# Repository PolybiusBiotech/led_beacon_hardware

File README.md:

# LED Beacon 🚀
> Upgrading cheap LED beacons for professional DMX/Art-Net stage control.

 <!-- Tip: Export a nice 3D render from KiCAD -->

## 🚀 Manufacturing Status
- [ ] **Design:** Completed
- [ ] **Prototyping:** In Progress
- [ ] **Production:** Pending

## 📋 Quick Specs
- **MCU:** ESP32-C3-WROOM-02
- **Power:** +12V ±30% @ 2A
- **Connectivity:** DMX512 via 5 pin XLRs and WiFi

## 📂 Project Structure
- `/hardware`: KiCAD project files (Version 9.0.7).
- `/firmware`: PlatformIO project (Arduino/ESP-IDF framework).
- `/mechanical`: 3D-printable housing (.STEP).
- `/docs`: Specification, schematics and design calculations.
<!-- test: for test scripts -->

## 🛠 Setup & Development

### Hardware
- **Library Dependencies:** All footprints/symbols are [local to the repo / use standard KiCAD libs].
- **CI/CD:** Schematics are automatically exported to `/docs` on every push.

### Firmware
1. Open the `/firmware` folder in **VS Code**.
2. Ensure the **PlatformIO** extension is installed.
3. Connect your hardware via USB C port and click **Upload**.

## User Guide

1. Apply power via DC connector, 12V ±30% from a 3A capable supply.
2. Attach to DMX chain with 2x XLR 5pin cables
   * If at the end of the bus use a terminator plug
3. Select a DMX address with the DIP switch
   * This light consumes 20 slots so avoid address above 492.
   * Ensure that this light is >20 slots away from the next lights.
4. Disable the WiFi AP with the DIP switch unless needed for diagnostics
5. Use your DMX controller to send packets on the DMX chain.
   * Slots 1 to 10 control the brightness per channel
     * `0x00` is off
     * `0xFF` is on
   * Slots 11 to 20 control the strobe effect per channel
     * `0x00` is fully on
     * `0x01` strobes at 0.2Hz
     * `0xFF` strobes at 20Hz
6. Enjoy!

---
*Commissioned for Null Sector for EMF Camp 2026.*

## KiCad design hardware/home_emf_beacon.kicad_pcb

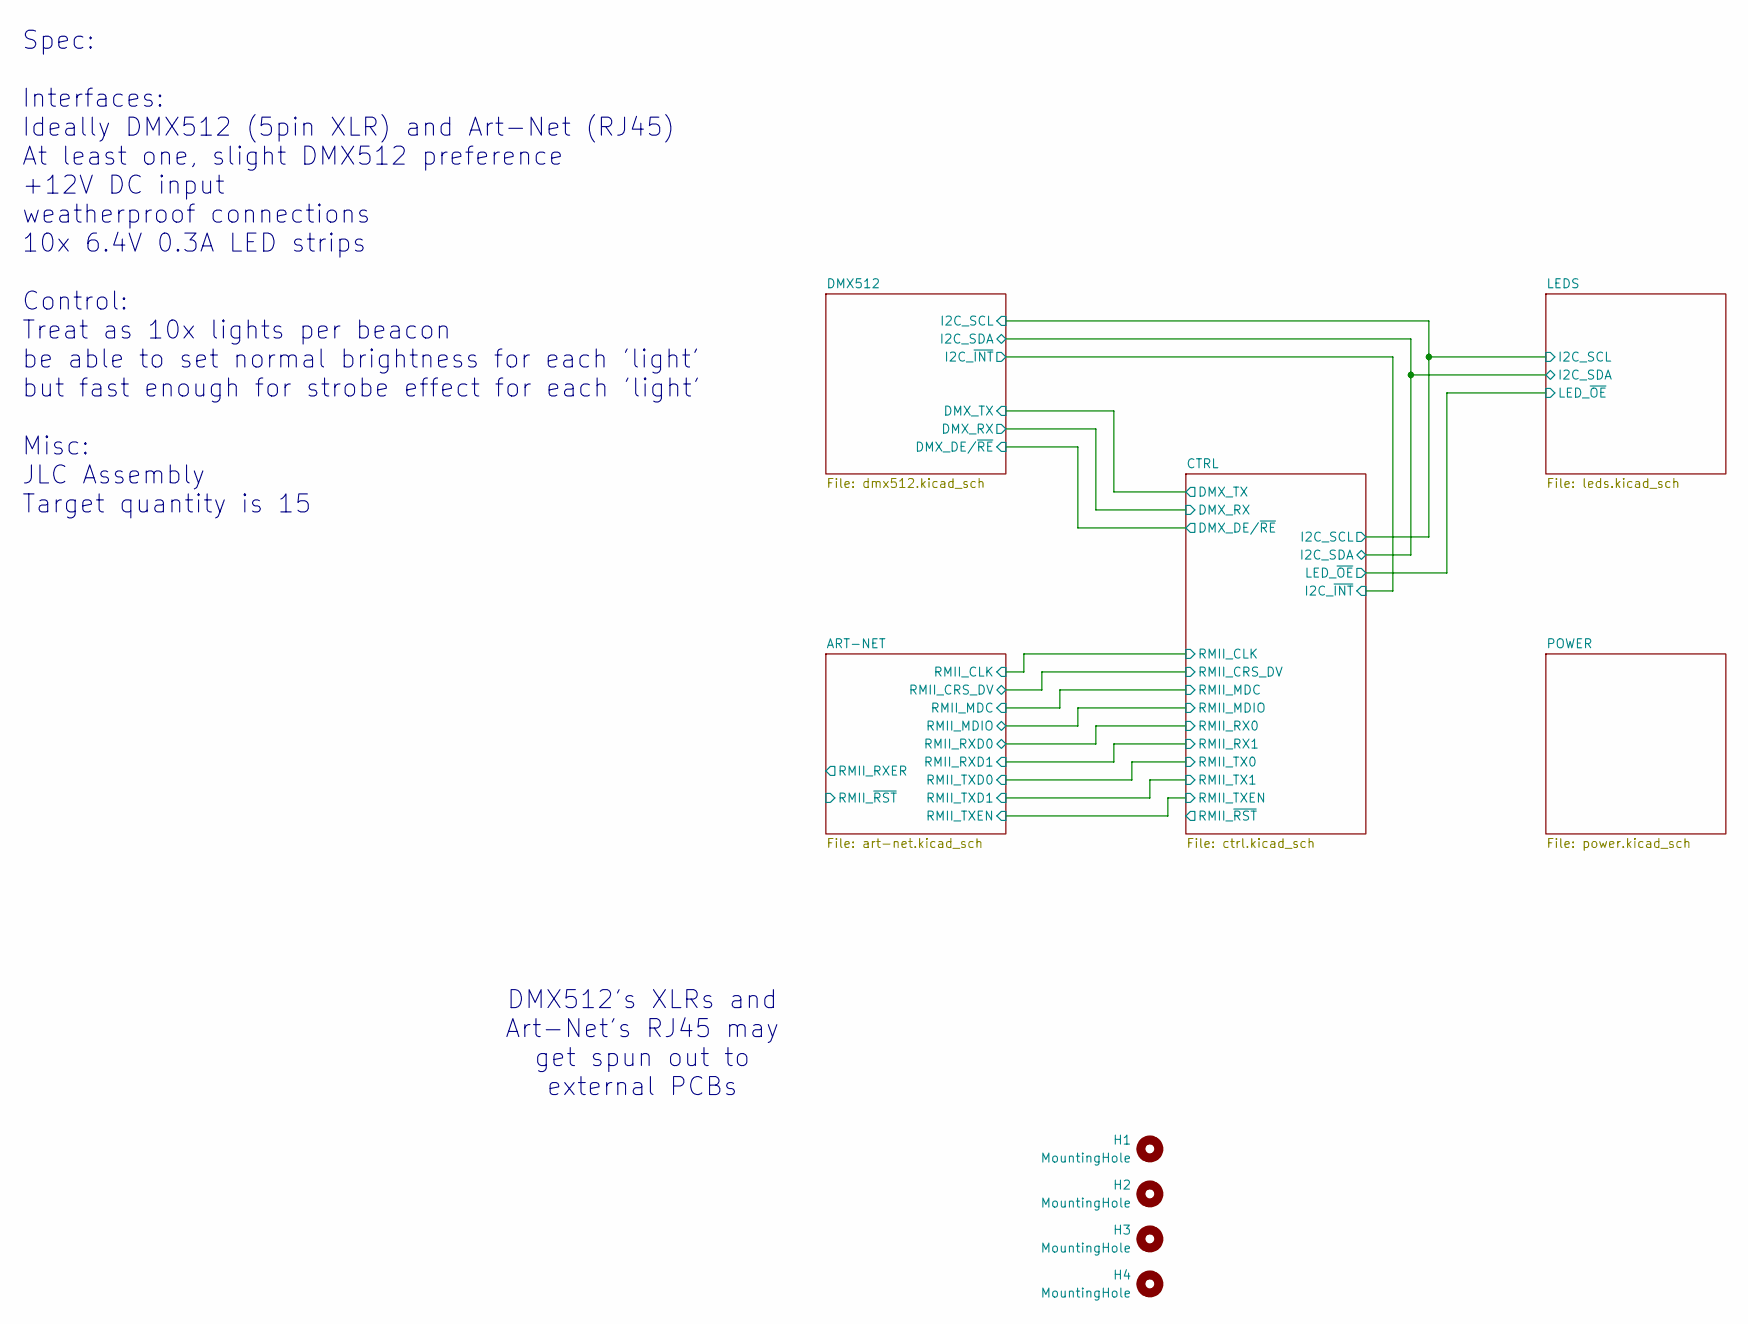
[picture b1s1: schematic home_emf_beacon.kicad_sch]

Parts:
H1, H2, H3, H4: MountingHole; MountingHole_4.3mm_M4

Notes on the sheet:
Spec: Interfaces: Ideally DMX512 (5pin XLR) and Art-Net (RJ45) At least one, slight DMX512 preference +12V DC input weatherproof connections 10x 6.4V 0.3A LED strips Control: Treat as 10x lights per beacon be able to set normal brightness for each 'light' but fast enough for strobe effect for each 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
DMX512's XLRs and Art-Net's RJ45 may get spun out to external PCBs

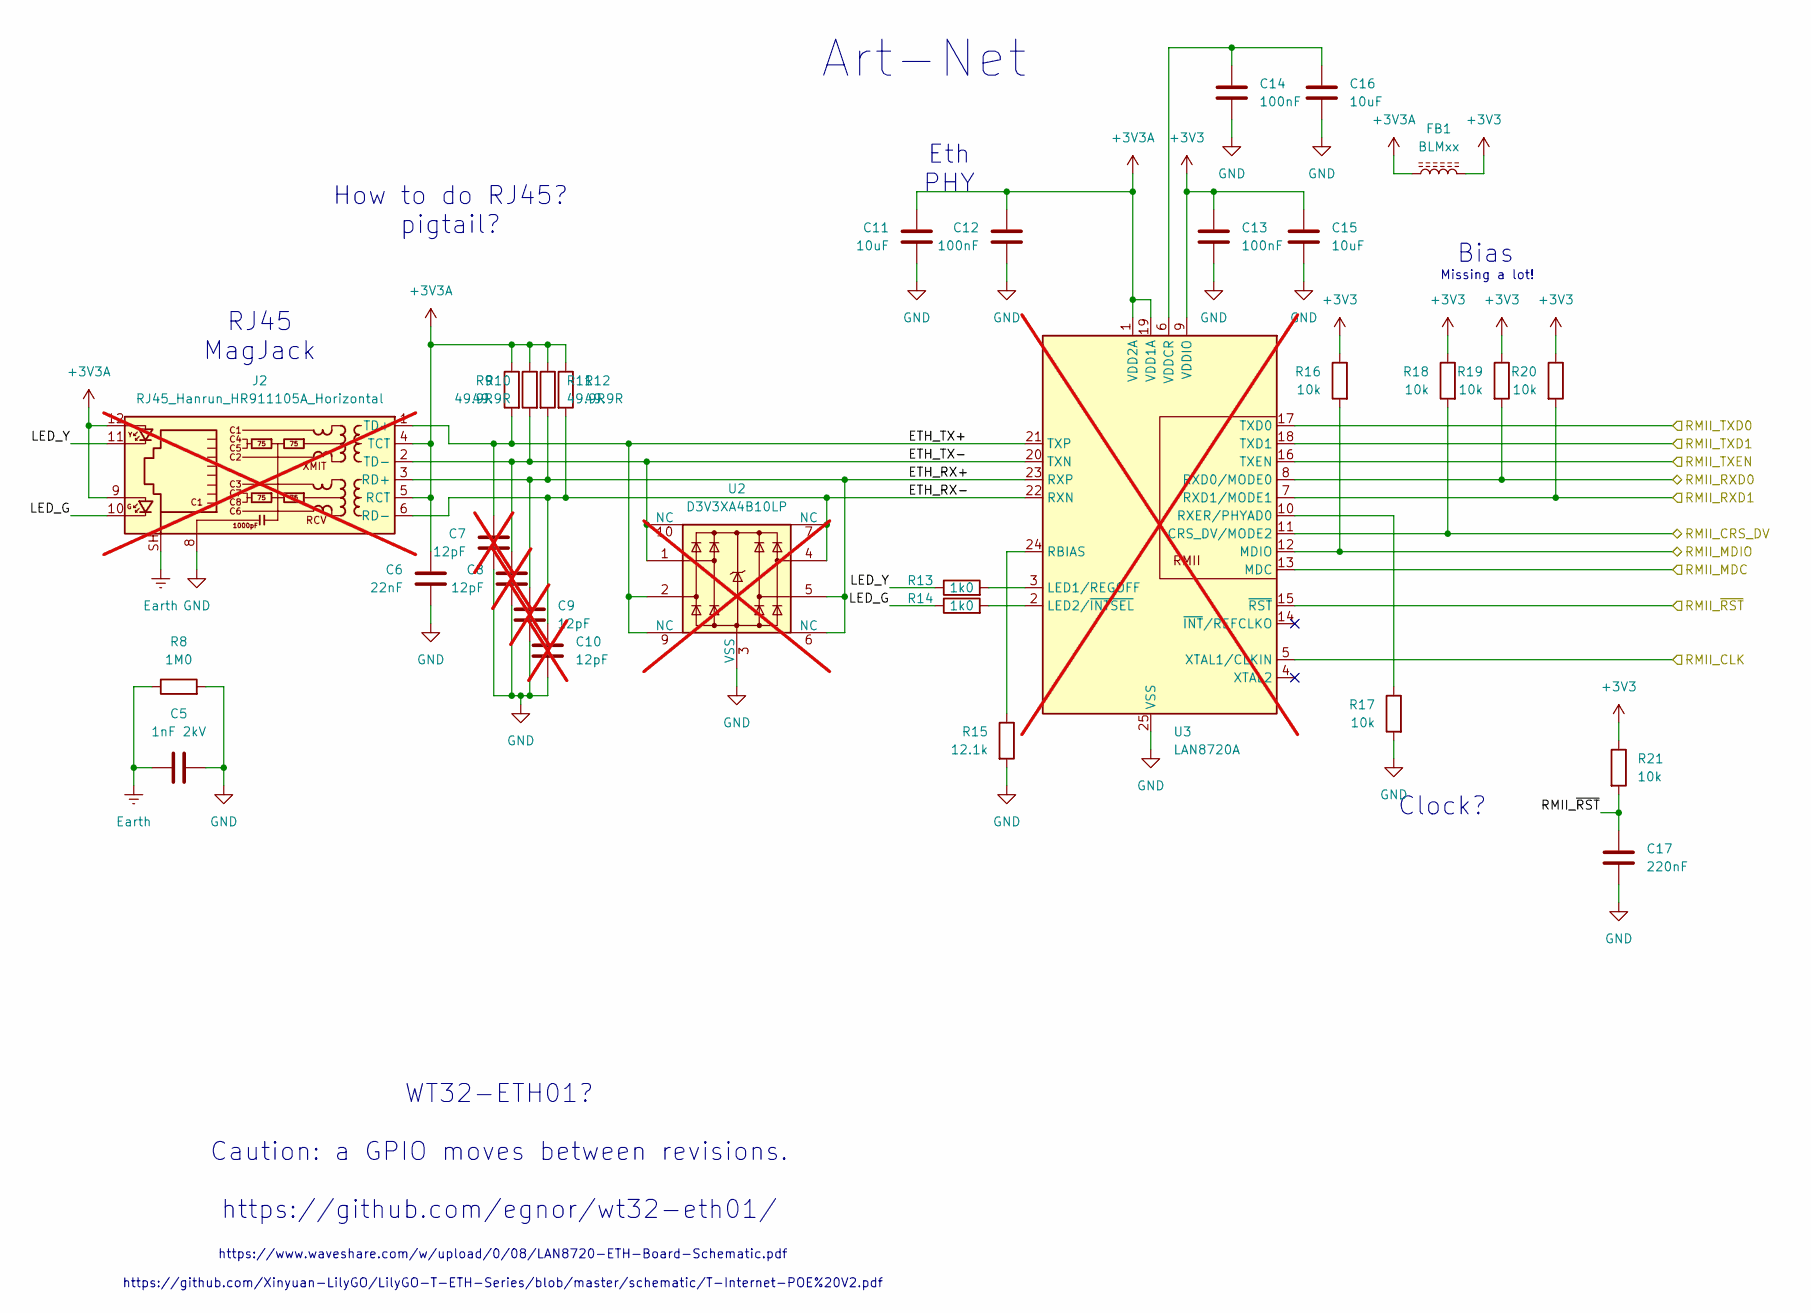
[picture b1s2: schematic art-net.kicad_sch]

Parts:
C5: 1nF 2kV; C_1808_4520Metric
C6: 22nF; C_0603_1608Metric
C7, C8, C9, C10: 12pF; C_0603_1608Metric; not fitted
C11, C15, C16: 10uF; C_0805_2012Metric
C12, C13, C14: 100nF; C_0603_1608Metric
C17: 220nF; C_0603_1608Metric
FB1: BLMxx; L_0603_1608Metric
J2: RJ45_Hanrun_HR911105A_Horizontal; LCSC C12074; not fitted
R8: 1M0; R_1206_3216Metric
R9, R10, R11, R12: 49.9R; R_0603_1608Metric
R13, R14: 1k0; R_0603_1608Metric
R15: 12.1k; R_0603_1608Metric
R16, R17, R18, R19, R20, R21: 10k; R_0603_1608Metric
U2: D3V3XA4B10LP; Diodes_UDFN-10_1x2.5mm_P0.5mm; not fitted
U3: LAN8720A; VQFN-24-1EP_4x4mm_P0.5mm_EP2.5x2.5mm_ThermalVias; not fitted

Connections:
+3V3: C13.2, C15.2, FB1.2, R16.1, R18.1, R19.1, R20.1, R21.1, U3.9 (VDDIO); also elsewhere on the board
+3V3A: C6.1, C11.2, C12.2, FB1.1, J2.4 (TCT), J2.5 (RCT), J2.9, J2.12, R9.1, R10.1, R11.1, R12.1, U3.1 (VDD2A), U3.19 (VDD1A)
/ART-NET/ETH_RX+: C9.1, J2.3 (RD+), R11.2, U2.5, U2.6 (NC), U3.23 (RXP)
/ART-NET/ETH_RX-: C10.1, J2.6 (RD-), R12.2, U2.4, U2.7 (NC), U3.22 (RXN)
/ART-NET/ETH_TX+: C7.1, J2.1 (TD+), R9.2, U2.2, U2.9 (NC), U3.21 (TXP)
/ART-NET/ETH_TX-: C8.1, J2.2 (TD-), R10.2, U2.1, U2.10 (NC), U3.20 (TXN)
/ART-NET/LED_G: J2.10, R14.1
/ART-NET/LED_Y: J2.11, R13.1
/ART-NET/RMII_~RST: C17.1, R21.2, U3.15 (~RST)
/CTRL/RMII_CLK: U3.5 (XTAL1/CLKIN); also elsewhere on the board
/CTRL/RMII_CRS_DV: R18.2, U3.11 (CRS_DV/MODE2); also elsewhere on the board
/CTRL/RMII_MDC: U3.13 (MDC); also elsewhere on the board
/CTRL/RMII_MDIO: R16.2, U3.12 (MDIO); also elsewhere on the board
/CTRL/RMII_RX0: R19.2, U3.8 (RXD0/MODE0); also elsewhere on the board
/CTRL/RMII_RX1: R20.2, U3.7 (RXD1/MODE1); also elsewhere on the board
/CTRL/RMII_TX0: U3.17 (TXD0); also elsewhere on the board
/CTRL/RMII_TX1: U3.18 (TXD1); also elsewhere on the board
/CTRL/RMII_TXEN: U3.16 (TXEN); also elsewhere on the board
Earth: C5.1, J2.SH, R8.1
GND: C5.2, C6.2, C7.2, C8.2, C9.2, C10.2, C11.1, C12.1, C13.1, C14.1, C15.1, C16.1, C17.2, J2.8, R8.2, R15.2, R17.2, U2.3 (VSS), U2.8 (VSS), U3.25 (VSS); also elsewhere on the board
unnamed: R13.2, U3.3 (LED1/REGOFF)
unnamed: R14.2, U3.2 (LED2/~INTSEL)
unnamed: R15.1, U3.24 (RBIAS)
unnamed: R17.1, U3.10 (RXER/PHYAD0)
unnamed: C14.2, C16.2, U3.6 (VDDCR)

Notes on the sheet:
How to do RJ45? pigtail?
Bias
WT32-ETH01? Caution: a GPIO moves between revisions. https://github.com/egnor/wt32-eth01/
https://www.waveshare.com/w/upload/0/08/LAN8720-ETH-Board-Schematic.pdf https://github.com/Xinyuan-LilyGO/LilyGO-T-ETH-Series/blob/master/schematic/T-Internet-POE%20V2.pdf
RJ45 MagJack
Art-Net
Eth PHY
Missing a lot!
Clock?

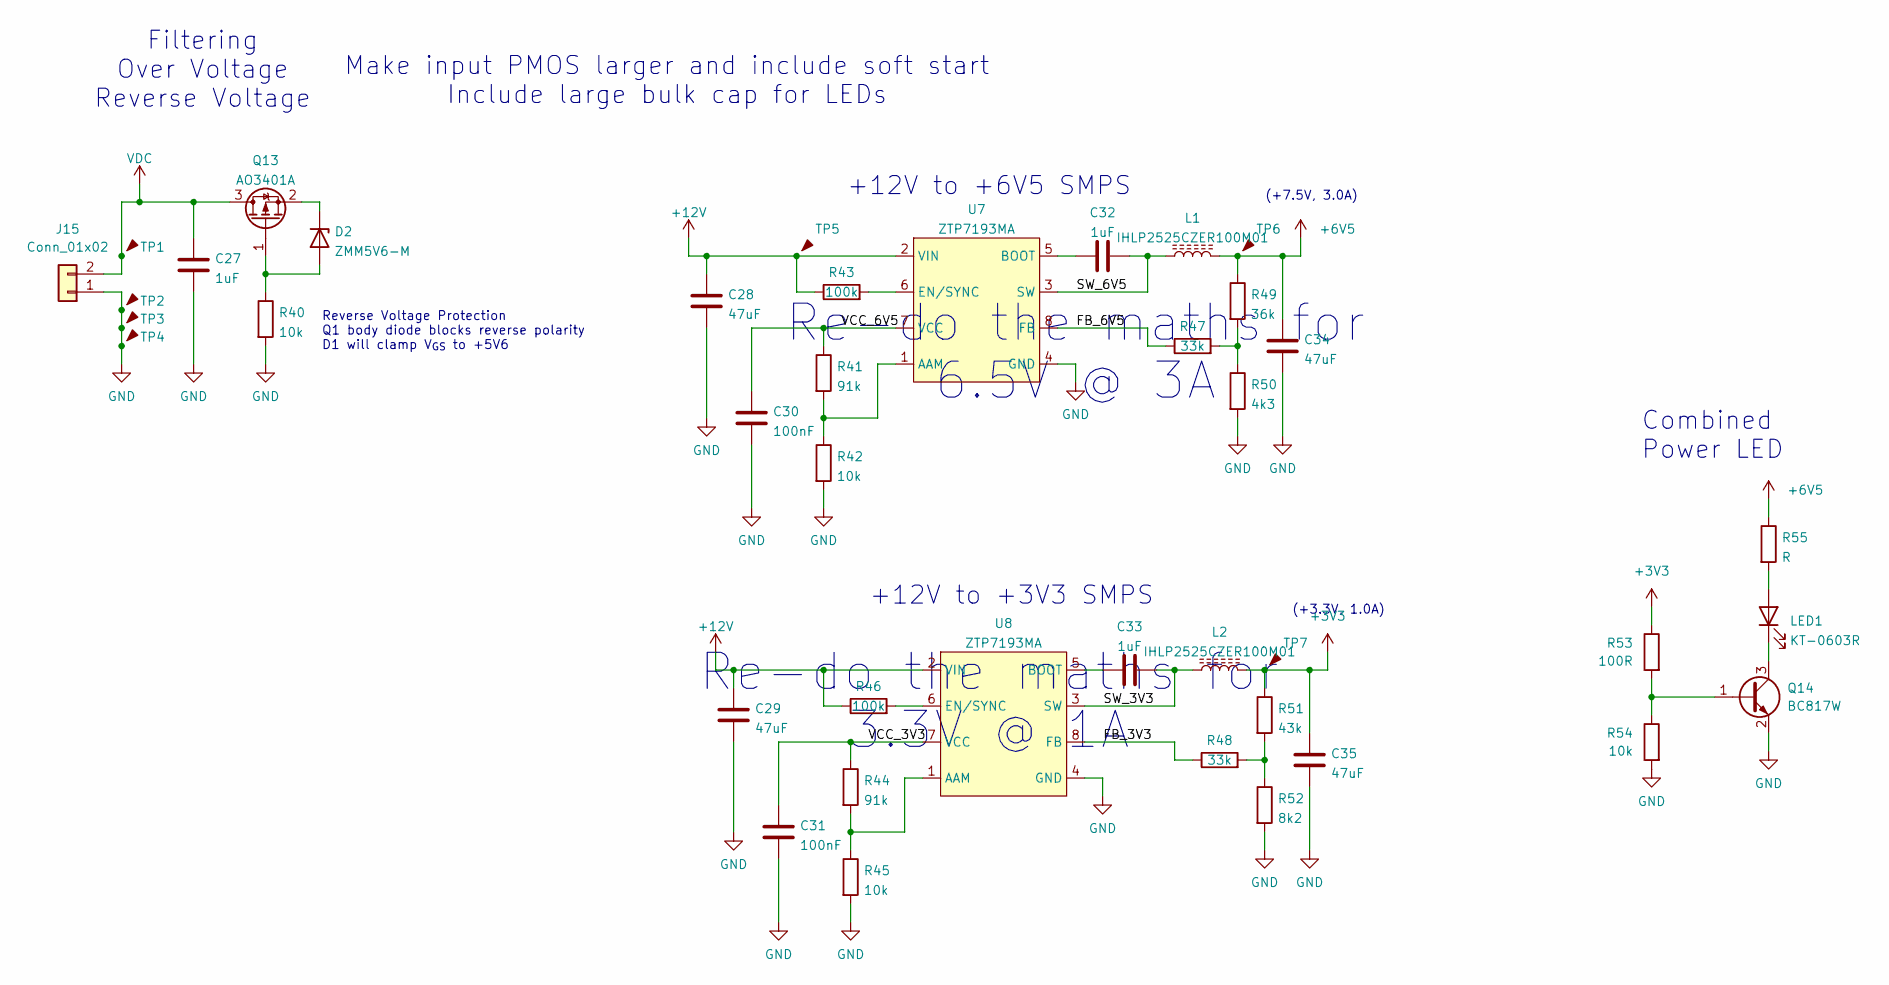
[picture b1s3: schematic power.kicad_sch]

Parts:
C27, C32, C33: 1uF; C_0603_1608Metric; Voltage 50V; LCSC C15849
C28, C29, C34, C35: 47uF; C_1210_3225Metric; Voltage 25V; LCSC C77101
C30, C31: 100nF; C_0603_1608Metric; Voltage 50V; LCSC C14663
D2: ZMM5V6-M; D_MiniMELF; LCSC C8062
J15: Conn_01x02; PhoenixContact_MSTBVA_2,5_2-G-5,08_1x02_P5.08mm_Vertical
L1, L2: IHLP2525CZER100M01; L_Vishay_IHLP-2525; LCSC C540965
LED1: KT-0603R; LED_0603_1608Metric; LCSC C2286
Q13: AO3401A; SOT-23; LCSC C15127
Q14: BC817W; SOT-323_SC-70
R40, R42, R45: 10k; R_0603_1608Metric; LCSC C25804
R41, R44: 91k; R_0603_1608Metric; LCSC C23265
R43, R46: 100k; R_0603_1608Metric; LCSC C25803
R47, R48: 33k; R_0603_1608Metric; LCSC C4216
R49: 36k; R_0603_1608Metric; LCSC C23147
R50: 4k3; R_0603_1608Metric; LCSC C23159
R51: 43k; R_0603_1608Metric; LCSC C23172
R52: 8k2; R_0603_1608Metric; LCSC C25981
R53: 100R; R_0603_1608Metric
R54: 10k; R_0603_1608Metric
R55: R; R_0603_1608Metric
TP1, TP2, TP3, TP4, TP5, TP6, TP7: TestPoint; TestPoint_Pad_D1.5mm
U7, U8: ZTP7193MA; SOT-23-8; LCSC C481284

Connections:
+3V3: C35.1, L2.2, R51.1, R53.1, TP7.1; also elsewhere on the board
+6V5: C34.1, L1.2, R49.1, R55.1, TP6.1; also elsewhere on the board
+12V: C28.1, C29.1, R43.1, R46.1, TP5.1, U7.2 (VIN), U8.2 (VIN)
/POWER/FB_3V3: R48.1, U8.8 (FB)
/POWER/FB_6V5: R47.1, U7.8 (FB)
/POWER/SW_3V3: C33.2, L2.1, U8.3 (SW)
/POWER/SW_6V5: C32.2, L1.1, U7.3 (SW)
/POWER/VCC_3V3: C31.2, R44.1, U8.7 (VCC)
/POWER/VCC_6V5: C30.2, R41.1, U7.7 (VCC)
GND: C27.2, C28.2, C29.2, C30.1, C31.1, C34.2, C35.2, J15.1, Q14.2 (E), R40.2, R42.2, R45.2, R50.2, R52.2, R54.2, TP2.1, TP3.1, TP4.1, U7.4 (GND), U8.4 (GND); also elsewhere on the board
unnamed: D2.2 (A), Q13.1 (G), R40.1
unnamed: D2.1 (K), Q13.2 (S)
unnamed: LED1.2 (A), R55.2
unnamed: LED1.1 (K), Q14.3 (C)
unnamed: Q14.1 (B), R53.2, R54.1
unnamed: R47.2, R49.2, R50.1
unnamed: R48.2, R51.2, R52.1
unnamed: R41.2, R42.1, U7.1 (AAM)
unnamed: C32.1, U7.5 (BOOT)
unnamed: R43.2, U7.6 (EN/SYNC)
unnamed: R44.2, R45.1, U8.1 (AAM)
unnamed: C33.1, U8.5 (BOOT)
unnamed: R46.2, U8.6 (EN/SYNC)
VDC: C27.1, J15.2, Q13.3 (D), TP1.1

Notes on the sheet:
Make input PMOS larger and include soft start Include large bulk cap for LEDs
(+7.5V, 3.0A)
Re-do the maths for 3.3V @ 1A
Re-do the maths for 6.5V @ 3A
Filtering Over Voltage Reverse Voltage
Combined Power LED
(+3.3V, 1.0A)
+12V to +3V3 SMPS
+12V to +6V5 SMPS
Reverse Voltage Protection Q1 body diode blocks reverse polarity D1 will clamp V_{GS} to +5V6

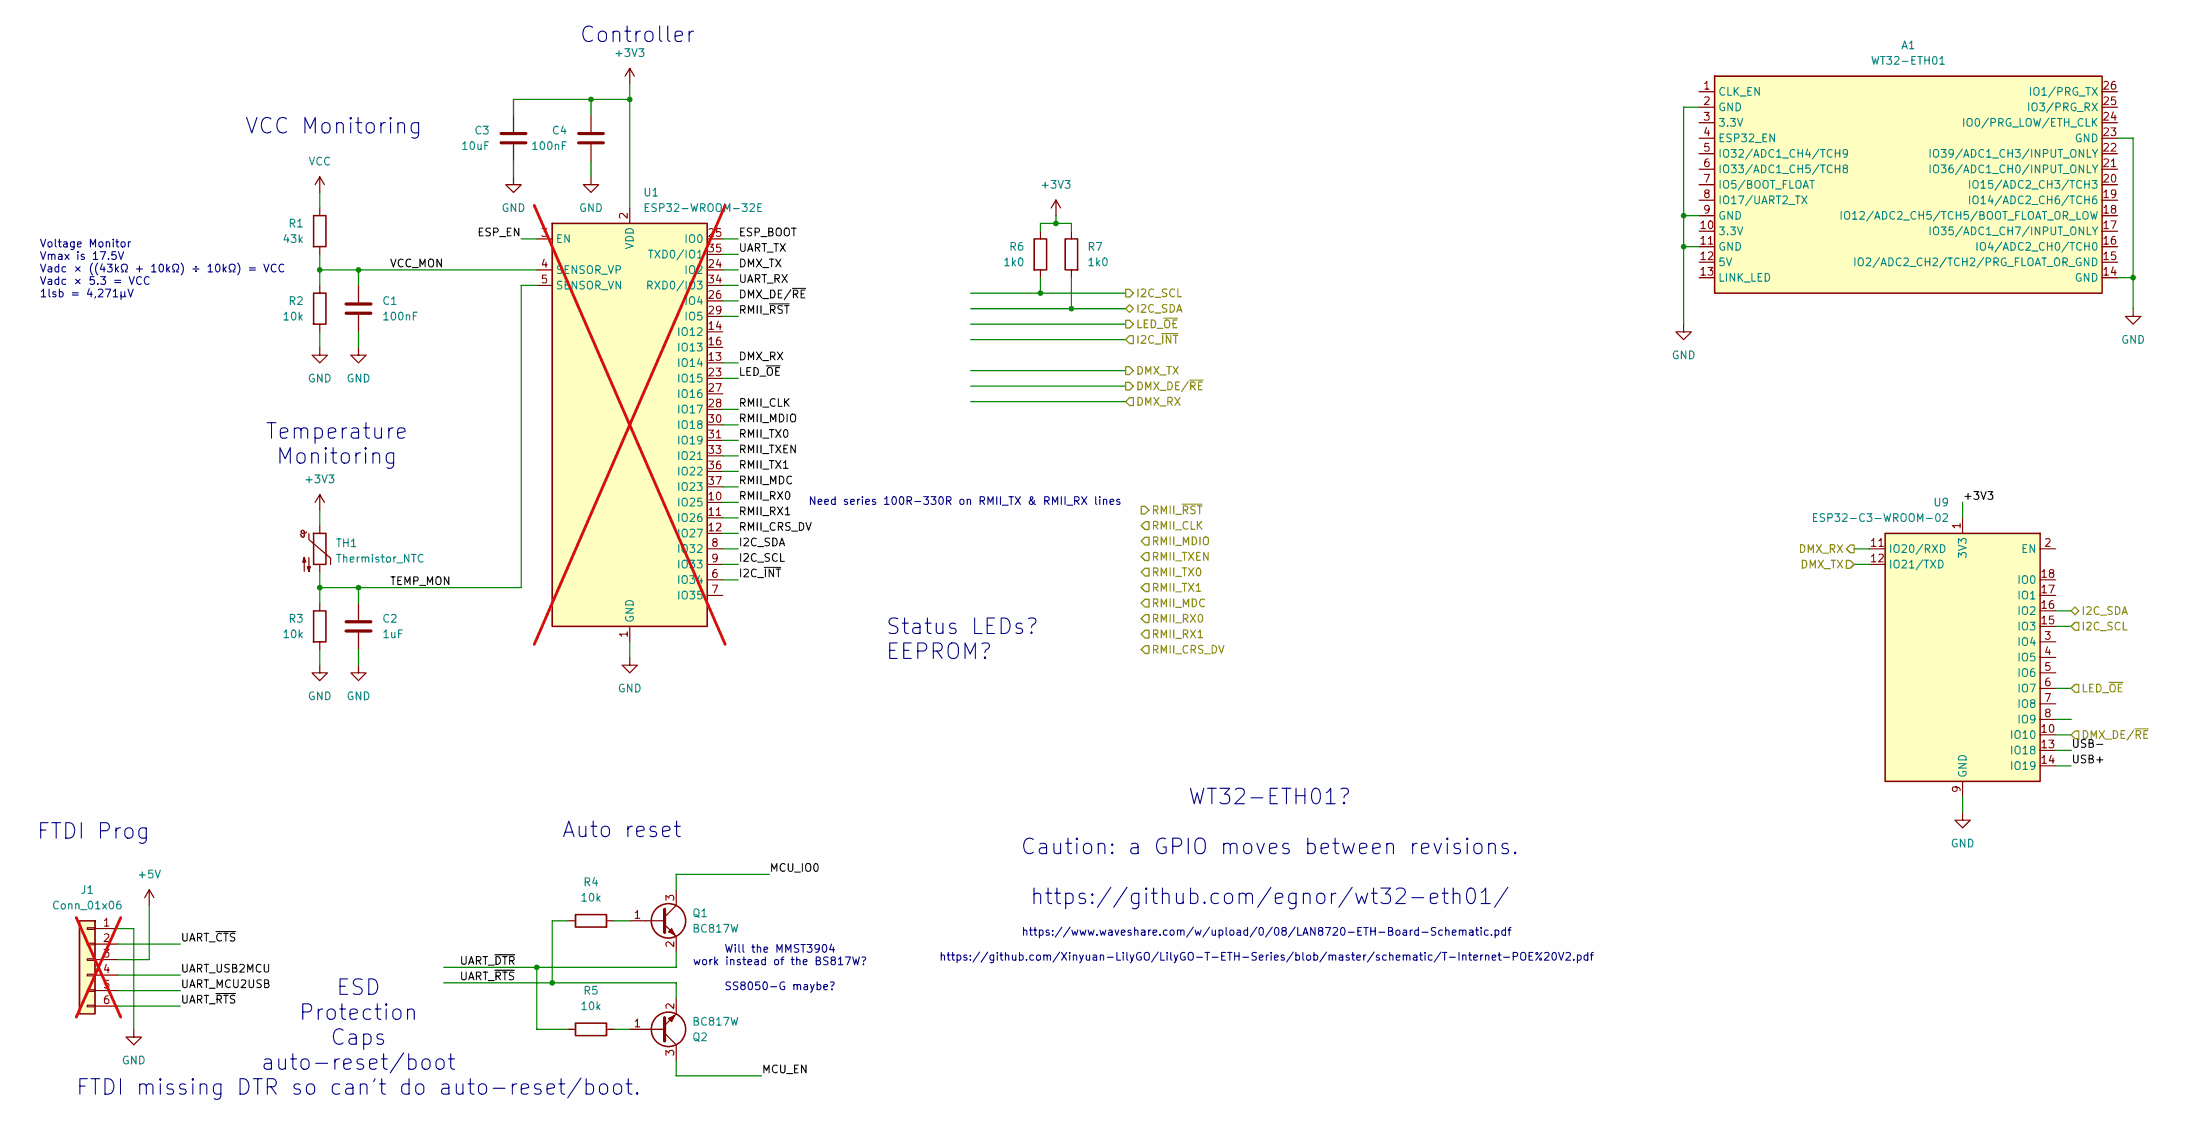
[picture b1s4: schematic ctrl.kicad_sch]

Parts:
A1: WT32-ETH01
C1, C4: 100nF; C_0603_1608Metric
C2: 1uF; C_0603_1608Metric
C3: 10uF; C_0805_2012Metric
J1: Conn_01x06; PinHeader_1x06_P2.54mm_Vertical; not fitted
Q1, Q2: BC817W; SOT-323_SC-70
R1: 43k; R_0603_1608Metric
R2, R3, R4, R5: 10k; R_0603_1608Metric
R6, R7: 1k0; R_0603_1608Metric
TH1: Thermistor_NTC; R_0603_1608Metric
U1: ESP32-WROOM-32E; ESP32-WROOM-32D; not fitted
U9: ESP32-C3-WROOM-02

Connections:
+3V3: C3.1, C4.1, R6.1, R7.1, TH1.1, U1.2 (VDD), U9.1 (3V3); also elsewhere on the board
+5V: J1.3
/CTRL/DMX_DE/~RE: U1.26 (IO4), U9.10 (IO10); also elsewhere on the board
/CTRL/DMX_RX: U1.13 (IO14), U9.11 (IO20/RXD); also elsewhere on the board
/CTRL/DMX_TX: U1.24 (IO2), U9.12 (IO21/TXD); also elsewhere on the board
/CTRL/ESP_BOOT: U1.25 (IO0)
/CTRL/ESP_EN: U1.3 (EN)
/CTRL/I2C_SCL: R6.2, U1.9 (IO33), U9.15 (IO3); also elsewhere on the board
/CTRL/I2C_SDA: R7.2, U1.8 (IO32), U9.16 (IO2); also elsewhere on the board
/CTRL/I2C_~INT: U1.6 (IO34); also elsewhere on the board
/CTRL/LED_~OE: U1.23 (IO15), U9.6 (IO7); also elsewhere on the board
/CTRL/MCU_EN: Q2.3 (C)
/CTRL/MCU_IO0: Q1.3 (C)
/CTRL/RMII_CLK: U1.28 (IO17); also elsewhere on the board
/CTRL/RMII_CRS_DV: U1.12 (IO27); also elsewhere on the board
/CTRL/RMII_MDC: U1.37 (IO23); also elsewhere on the board
/CTRL/RMII_MDIO: U1.30 (IO18); also elsewhere on the board
/CTRL/RMII_RX0: U1.10 (IO25); also elsewhere on the board
/CTRL/RMII_RX1: U1.11 (IO26); also elsewhere on the board
/CTRL/RMII_TX0: U1.31 (IO19); also elsewhere on the board
/CTRL/RMII_TX1: U1.36 (IO22); also elsewhere on the board
/CTRL/RMII_TXEN: U1.33 (IO21); also elsewhere on the board
/CTRL/RMII_~RST: U1.29 (IO5)
/CTRL/TEMP_MON: C2.1, R3.1, TH1.2, U1.5 (SENSOR_VN)
/CTRL/UART_MCU2USB: J1.5
/CTRL/UART_RX: U1.34 (RXD0/IO3)
/CTRL/UART_TX: U1.35 (TXD0/IO1)
/CTRL/UART_USB2MCU: J1.4
/CTRL/UART_~CTS: J1.2
/CTRL/UART_~DTR: Q1.2 (E), R5.1
/CTRL/UART_~RTS: J1.6, Q2.2 (E), R4.1
/CTRL/USB+: U9.14 (IO19)
/CTRL/USB-: U9.13 (IO18)
/CTRL/VCC_MON: C1.1, R1.2, R2.1, U1.4 (SENSOR_VP)
GND: A1.2 (GND), A1.9 (GND), A1.11 (GND), A1.14 (GND), A1.23 (GND), C1.2, C2.2, C3.2, C4.2, J1.1, R2.2, R3.2, U1.1 (GND), U1.15 (GND), U1.38 (GND), U1.39 (GND), U9.9 (GND), U9.19 (GND); also elsewhere on the board
unnamed: Q1.1 (B), R4.2
unnamed: Q2.1 (B), R5.2
VCC: R1.1

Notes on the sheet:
Auto reset
Status LEDs? EEPROM?
WT32-ETH01? Caution: a GPIO moves between revisions. https://github.com/egnor/wt32-eth01/
VCC Monitoring
Need series 100R-330R on RMII_TX & RMII_RX lines
Will the MMST3904 work instead of the BS817W? SS8050-G maybe?
https://www.waveshare.com/w/upload/0/08/LAN8720-ETH-Board-Schematic.pdf https://github.com/Xinyuan-LilyGO/LilyGO-T-ETH-Series/blob/master/schematic/T-Internet-POE%20V2.pdf
Temperature Monitoring
Controller
FTDI Prog
ESD Protection Caps auto-reset/boot FTDI missing DTR so can't do auto-reset/boot.
Voltage Monitor Vmax is 17.5V Vadc × ((43kΩ + 10kΩ) ÷ 10kΩ) = VCC Vadc × 5.3 = VCC 1lsb = 4,271μV

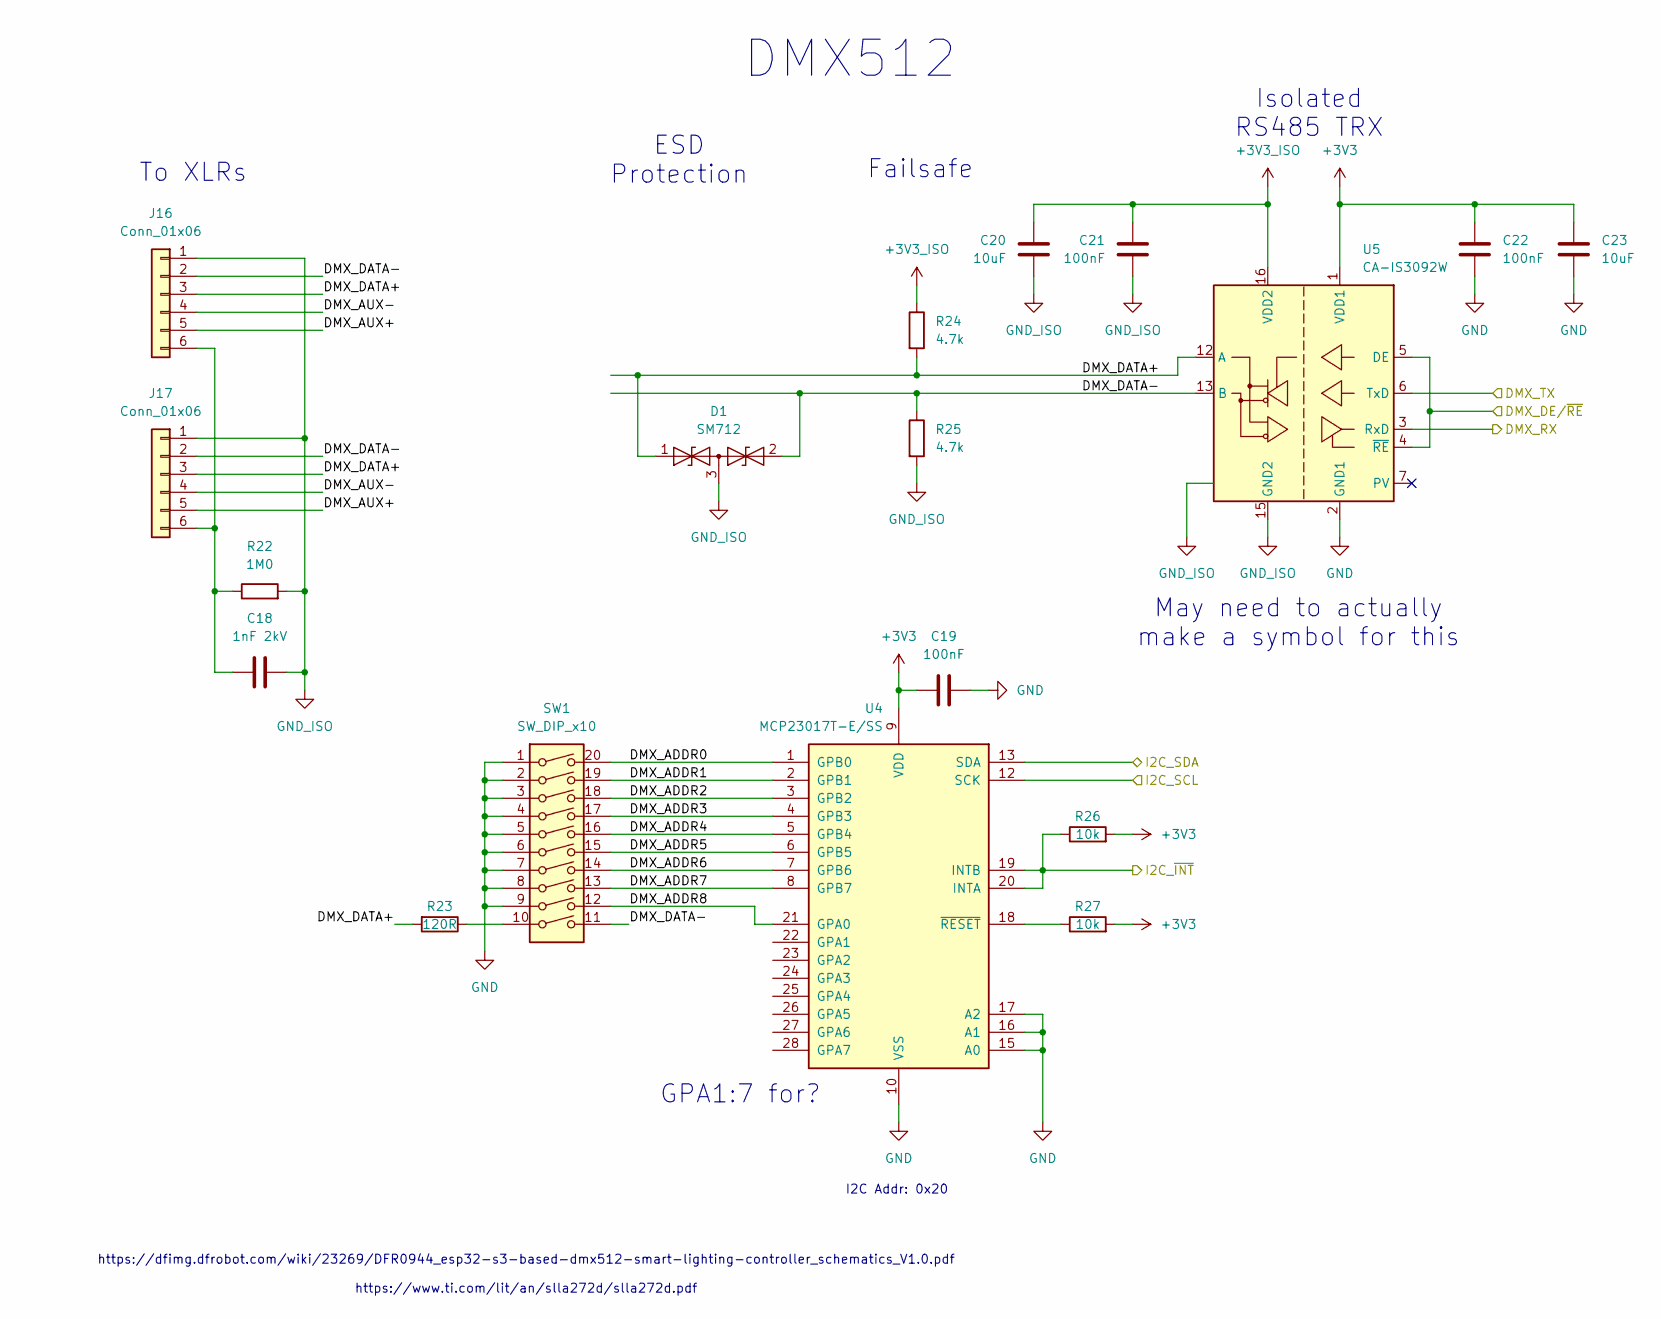
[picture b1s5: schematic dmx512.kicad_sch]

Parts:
C18: 1nF 2kV; C_1808_4520Metric
C19, C21, C22: 100nF; C_0603_1608Metric
C20, C23: 10uF; C_0805_2012Metric
D1: SM712; SOT-23; LCSC C7420375
J16, J17: Conn_01x06; JST_PH_B6B-PH-K_1x06_P2.00mm_Vertical
R22: 1M0; R_1206_3216Metric
R23: 120R; R_0805_2012Metric_Pad1.20x1.40mm_HandSolder
R24, R25: 4.7k; R_0603_1608Metric
R26, R27: 10k; R_0603_1608Metric
SW1: SW_DIP_x10; SW_DIP_SPSTx10_Slide_6.7x26.96mm_W7.62mm_P2.54mm_LowProfile; LCSC C509577
U4: MCP23017T-E/SS; SSOP-28_5.3x10.2mm_P0.65mm; LCSC C558584
U5: CA-IS3092W; SOIC-16W_7.5x10.3mm_P1.27mm; LCSC C2890051

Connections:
+3V3: C19.2, C22.1, C23.1, R26.2, R27.2, U4.9 (VDD), U5.1 (VDD1); also elsewhere on the board
+3V3_ISO: C20.1, C21.1, R24.1, U5.16 (VDD2)
/CTRL/DMX_DE/~RE: U5.4 (~RE), U5.5 (DE); also elsewhere on the board
/CTRL/DMX_RX: U5.3 (RxD); also elsewhere on the board
/CTRL/DMX_TX: U5.6 (TxD); also elsewhere on the board
/CTRL/I2C_SCL: U4.12 (SCK); also elsewhere on the board
/CTRL/I2C_SDA: U4.13 (SDA); also elsewhere on the board
/CTRL/I2C_~INT: R26.1, U4.19 (INTB), U4.20 (INTA); also elsewhere on the board
/DMX512/DMX_ADDR0: SW1.20, U4.1 (GPB0)
/DMX512/DMX_ADDR1: SW1.19, U4.2 (GPB1)
/DMX512/DMX_ADDR2: SW1.18, U4.3 (GPB2)
/DMX512/DMX_ADDR3: SW1.17, U4.4 (GPB3)
/DMX512/DMX_ADDR4: SW1.16, U4.5 (GPB4)
/DMX512/DMX_ADDR5: SW1.15, U4.6 (GPB5)
/DMX512/DMX_ADDR6: SW1.14, U4.7 (GPB6)
/DMX512/DMX_ADDR7: SW1.13, U4.8 (GPB7)
/DMX512/DMX_ADDR8: SW1.12, U4.21 (GPA0)
/DMX512/DMX_AUX+: J16.5, J17.5
/DMX512/DMX_AUX-: J16.4, J17.4
/DMX512/DMX_DATA+: D1.1 (A1), J16.3, J17.3, R23.2, R24.2, U5.12 (A)
/DMX512/DMX_DATA-: D1.2 (A2), J16.2, J17.2, R25.1, SW1.11, U5.13 (B)
GND: C19.1, C22.2, C23.2, SW1.1, SW1.2, SW1.3, SW1.4, SW1.5, SW1.6, SW1.7, SW1.8, SW1.9, U4.10 (VSS), U4.15 (A0), U4.16 (A1), U4.17 (A2), U5.2 (GND1), U5.8 (GND1); also elsewhere on the board
GND_ISO: C18.2, C20.2, C21.2, D1.3 (common), J16.1, J17.1, R22.2, R25.2, U5.9 (GND2), U5.15 (GND2)
unnamed: C18.1, J16.6, J17.6, R22.1
unnamed: R23.1, SW1.10
unnamed: R27.1, U4.18 (~RESET)

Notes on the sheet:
May need to actually make a symbol for this
I2C Addr: 0x20
Failsafe
DMX512
https://dfimg.dfrobot.com/wiki/23269/DFR0944_esp32-s3-based-dmx512-smart-lighting-controller_schematics_V1.0.pdf https://www.ti.com/lit/an/slla272d/slla272d.pdf
To XLRs
ESD Protection
GPA1:7 for?
Isolated RS485 TRX

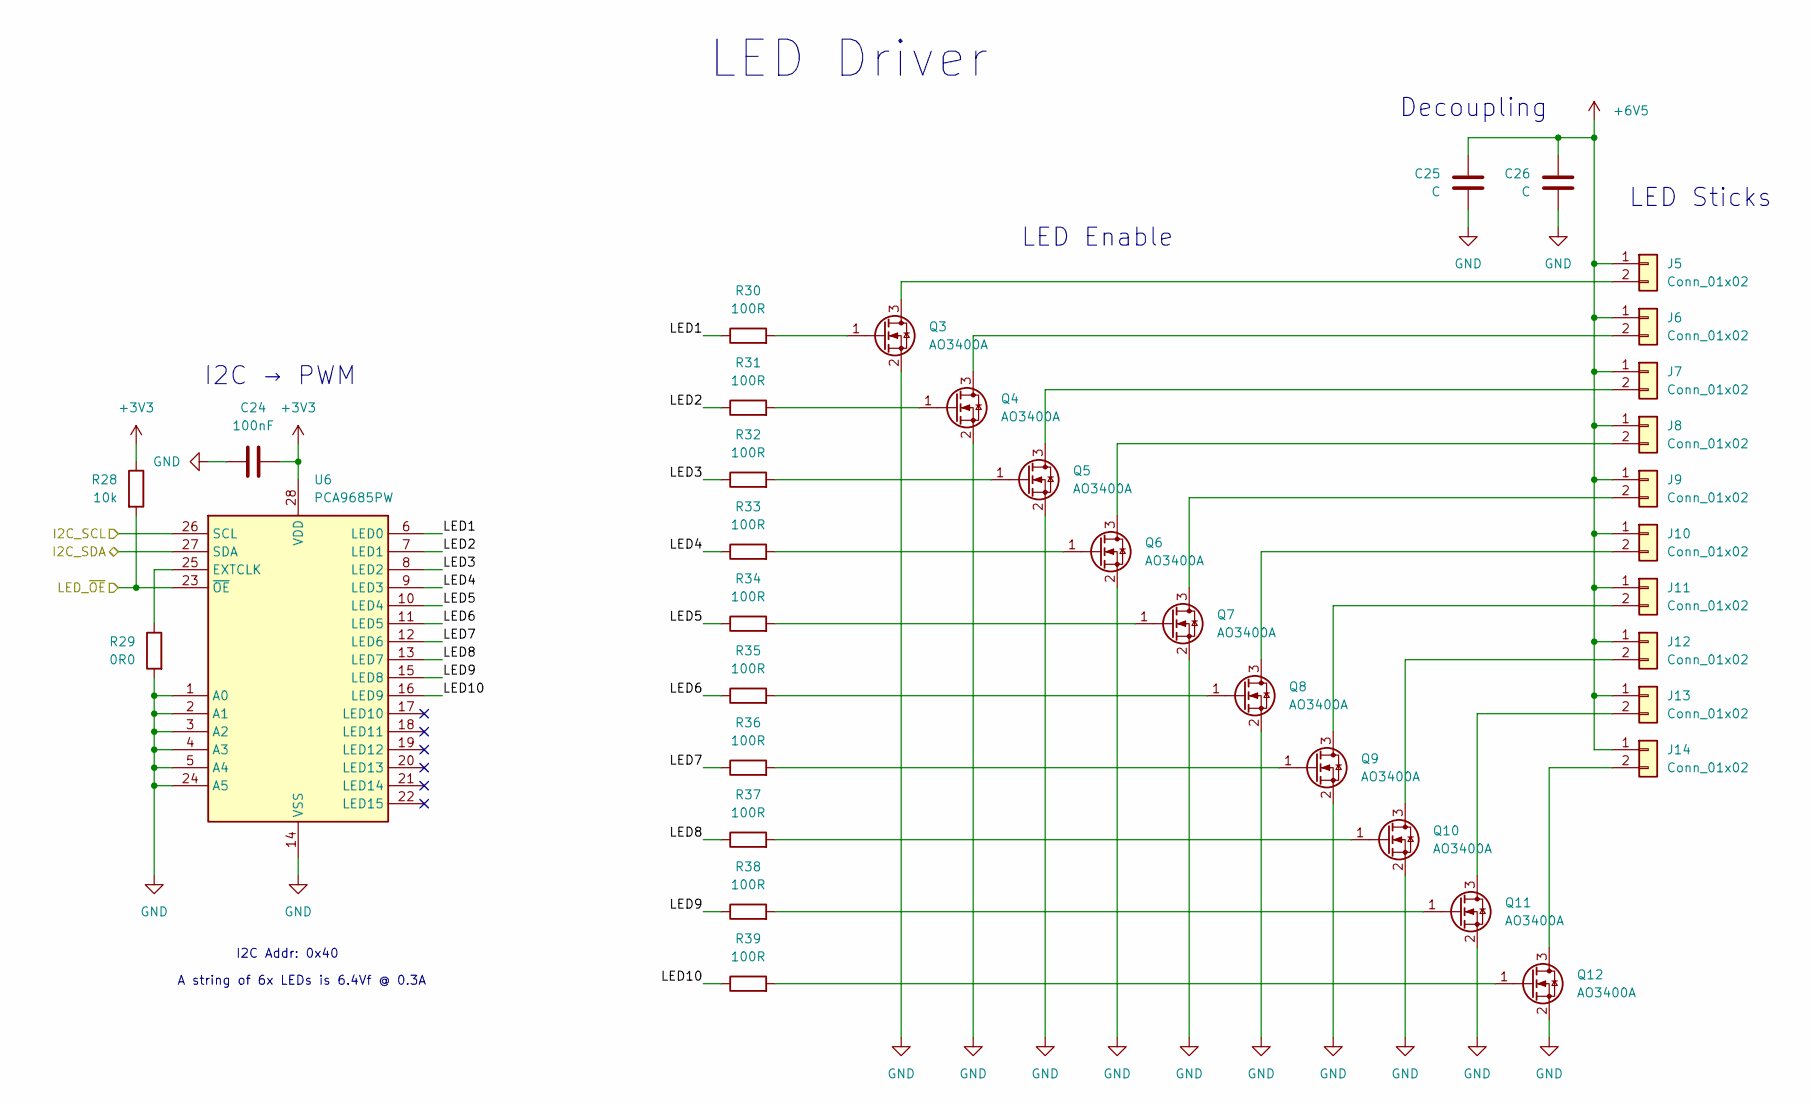
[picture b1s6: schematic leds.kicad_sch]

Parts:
C24: 100nF; C_0603_1608Metric
C25, C26: C
J5, J6, J7, J8, J9, J10, J11, J12, J13, J14: Conn_01x02; LED_Stick
Q3, Q4, Q5, Q6, Q7, Q8, Q9, Q10, Q11, Q12: AO3400A; SOT-23; LCSC C20917
R28: 10k; R_0603_1608Metric
R29: 0R0; R_0603_1608Metric
R30, R31, R32, R33, R34, R35, R36, R37, R38, R39: 100R; R_0603_1608Metric
U6: PCA9685PW; TSSOP-28_4.4x9.7mm_P0.65mm; LCSC C92206

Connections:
+3V3: C24.2, R28.1, U6.28 (VDD); also elsewhere on the board
+6V5: C25.1, C26.1, J5.1, J6.1, J7.1, J8.1, J9.1, J10.1, J11.1, J12.1, J13.1, J14.1; also elsewhere on the board
/CTRL/I2C_SCL: U6.26 (SCL); also elsewhere on the board
/CTRL/I2C_SDA: U6.27 (SDA); also elsewhere on the board
/CTRL/LED_~OE: R28.2, U6.23 (~OE); also elsewhere on the board
/LEDS/LED1: R30.1, U6.6 (LED0)
/LEDS/LED2: R31.1, U6.7 (LED1)
/LEDS/LED3: R32.1, U6.8 (LED2)
/LEDS/LED4: R33.1, U6.9 (LED3)
/LEDS/LED5: R34.1, U6.10 (LED4)
/LEDS/LED6: R35.1, U6.11 (LED5)
/LEDS/LED7: R36.1, U6.12 (LED6)
/LEDS/LED8: R37.1, U6.13 (LED7)
/LEDS/LED9: R38.1, U6.15 (LED8)
/LEDS/LED10: R39.1, U6.16 (LED9)
GND: C24.1, C25.2, C26.2, Q3.2 (S), Q4.2 (S), Q5.2 (S), Q6.2 (S), Q7.2 (S), Q8.2 (S), Q9.2 (S), Q10.2 (S), Q11.2 (S), Q12.2 (S), R29.2, U6.1 (A0), U6.2 (A1), U6.3 (A2), U6.4 (A3), U6.5 (A4), U6.14 (VSS), U6.24 (A5); also elsewhere on the board
unnamed: J5.2, Q3.3 (D)
unnamed: J6.2, Q4.3 (D)
unnamed: J7.2, Q5.3 (D)
unnamed: J8.2, Q6.3 (D)
unnamed: J9.2, Q7.3 (D)
unnamed: J10.2, Q8.3 (D)
unnamed: J11.2, Q9.3 (D)
unnamed: J12.2, Q10.3 (D)
unnamed: J13.2, Q11.3 (D)
unnamed: J14.2, Q12.3 (D)
unnamed: Q3.1 (G), R30.2
unnamed: Q4.1 (G), R31.2
unnamed: Q5.1 (G), R32.2
unnamed: Q6.1 (G), R33.2
unnamed: Q7.1 (G), R34.2
unnamed: Q8.1 (G), R35.2
unnamed: Q9.1 (G), R36.2
unnamed: Q10.1 (G), R37.2
unnamed: Q11.1 (G), R38.2
unnamed: Q12.1 (G), R39.2
unnamed: R29.1, U6.25 (EXTCLK)

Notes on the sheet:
I2C → PWM
A string of 6x LEDs is 6.4Vf @ 0.3A
I2C Addr: 0x40
LED Enable
LED Driver
LED Sticks
Decoupling
